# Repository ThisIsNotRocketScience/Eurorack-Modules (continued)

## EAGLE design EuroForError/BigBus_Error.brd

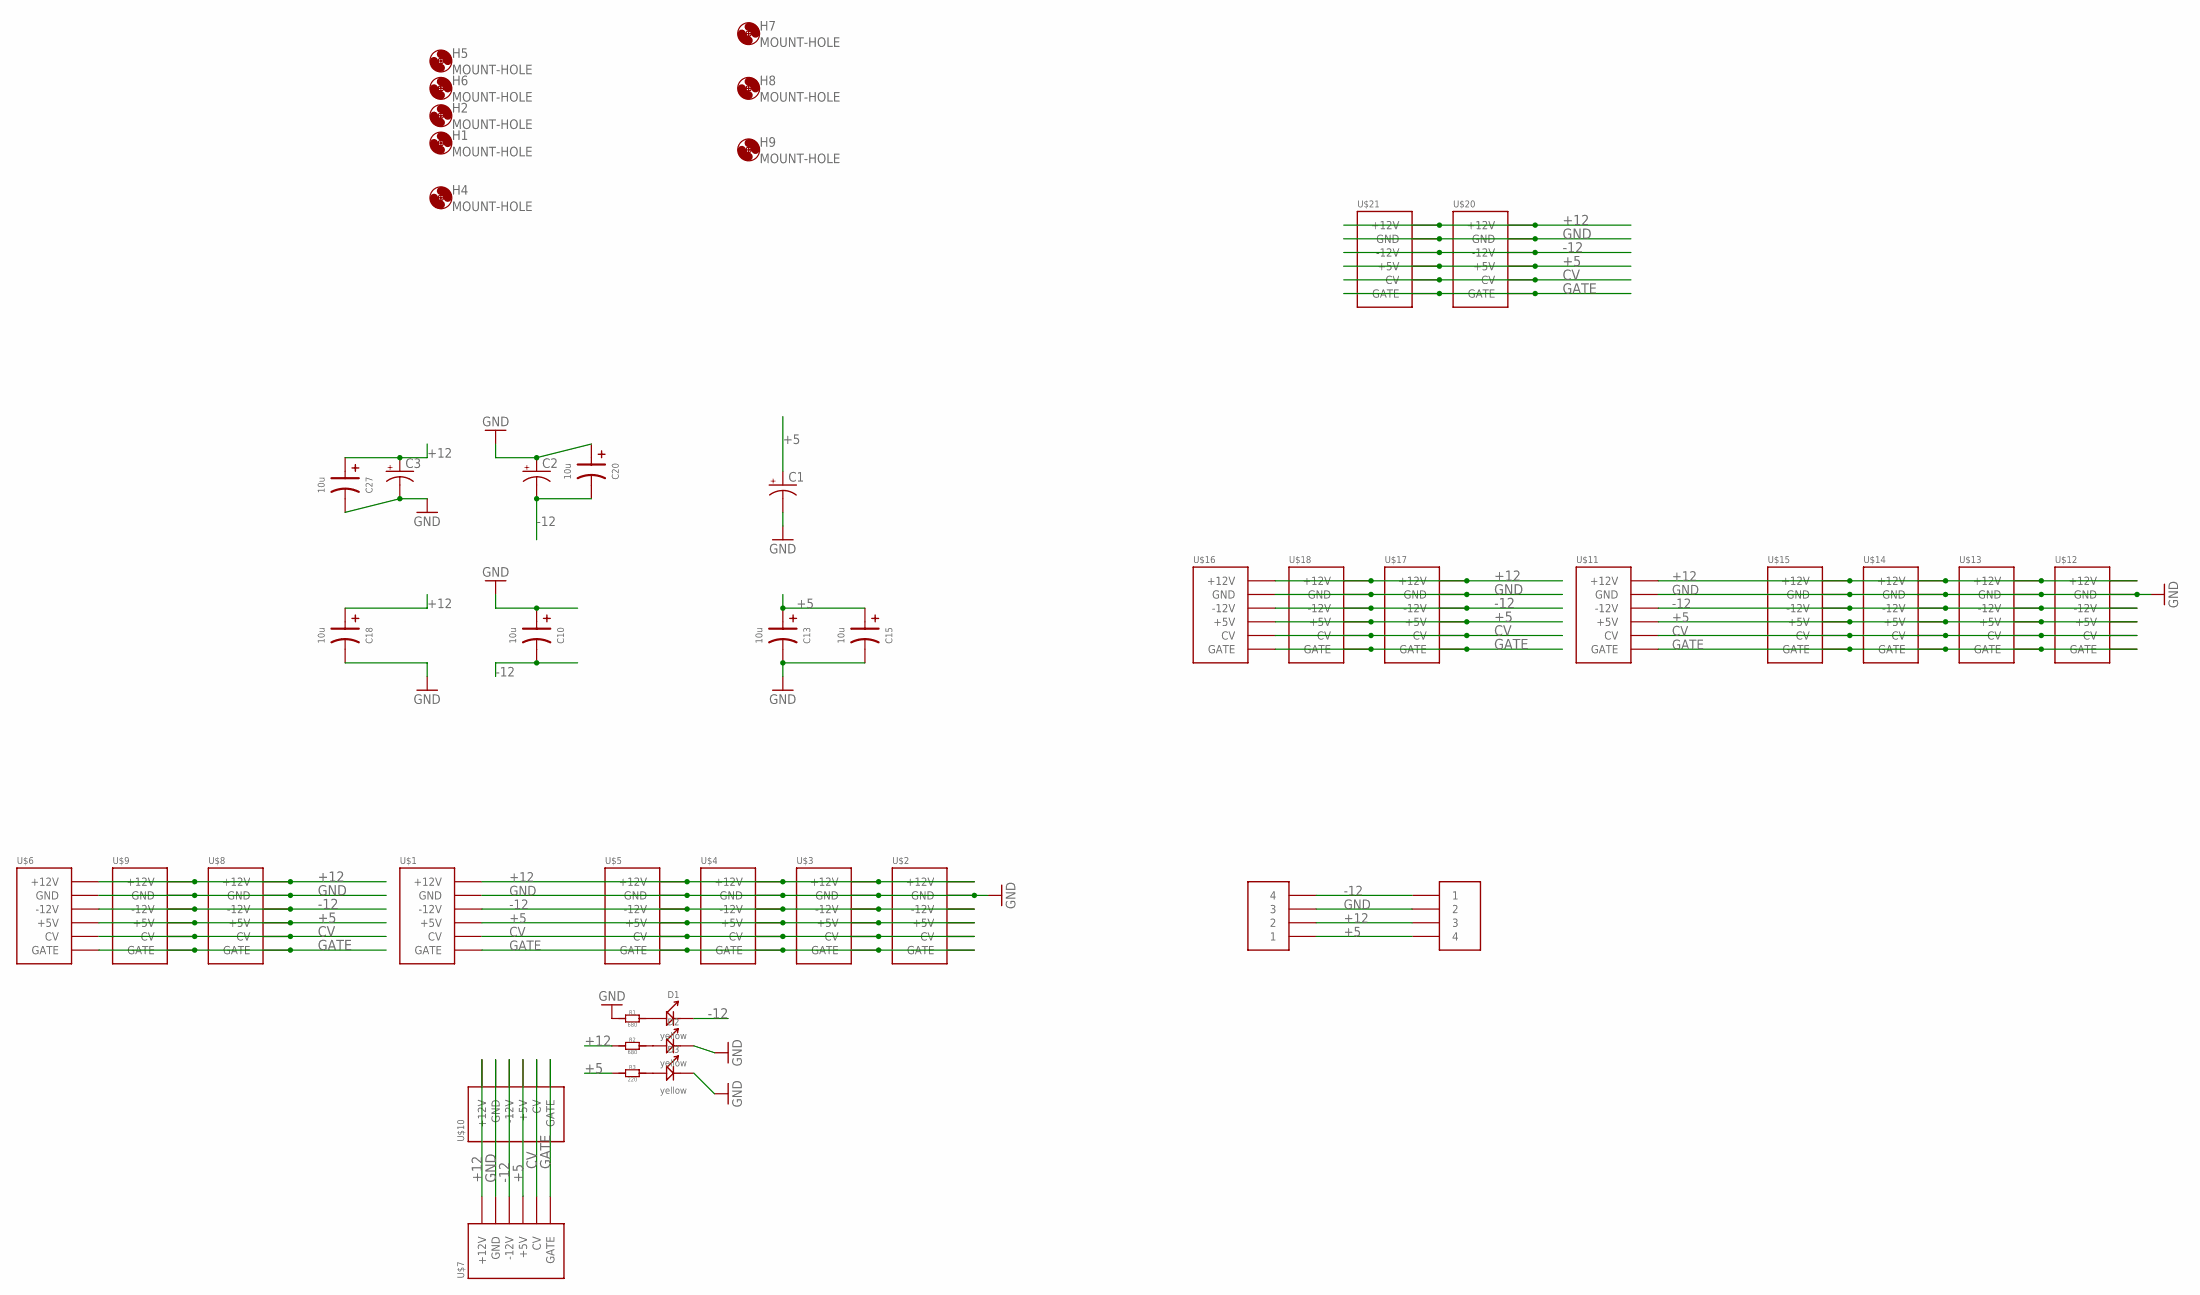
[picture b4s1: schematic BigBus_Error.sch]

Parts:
C1, C2, C3: CAP_POLD; PANASONIC_D
C10, C13, C15, C18, C20, C27: 10u; AVX-A
D1, D2, D3: yellow; LED0603
H1, H2, H4, H5, H6, H7, H8, H9: MOUNT-HOLE; 3.2-NOMARKINGS-SMALLSAFEZONE
R1, R2: 680; R0603
R3: 220; R0603
U$1, U$2, U$3, U$4, U$5, U$6, U$7, U$8, U$9, U$10, U$11, U$12, U$13, U$14, U$15, U$16, U$17, U$18, U$20, U$21: POWER_SHROUDED_NOTEXT; POWER_16_SHROUDED_NOTEXT
U$19, U$22: 4PIN5MM

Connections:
+5: C1.+, C13.+ (1), C15.+ (1), R3.1, U$1.11 (+5V), U$1.12 (+5V), U$2.11 (+5V), U$2.12 (+5V), U$3.11 (+5V), U$3.12 (+5V), U$4.11 (+5V), U$4.12 (+5V), U$5.11 (+5V), U$5.12 (+5V), U$6.11 (+5V), U$6.12 (+5V), U$7.11 (+5V), U$7.12 (+5V), U$8.11 (+5V), U$8.12 (+5V), U$9.11 (+5V), U$9.12 (+5V), U$10.11 (+5V), U$10.12 (+5V), U$11.11 (+5V), U$11.12 (+5V), U$12.11 (+5V), U$12.12 (+5V), U$13.11 (+5V), U$13.12 (+5V), U$14.11 (+5V), U$14.12 (+5V), U$15.11 (+5V), U$15.12 (+5V), U$16.11 (+5V), U$16.12 (+5V), U$17.11 (+5V), U$17.12 (+5V), U$18.11 (+5V), U$18.12 (+5V), U$19.4, U$20.11 (+5V), U$20.12 (+5V), U$21.11 (+5V), U$21.12 (+5V), U$22.1
+12: C3.+, C18.+ (1), C27.+ (1), R2.1, U$1.9 (+12V), U$1.10 (+12V), U$2.9 (+12V), U$2.10 (+12V), U$3.9 (+12V), U$3.10 (+12V), U$4.9 (+12V), U$4.10 (+12V), U$5.9 (+12V), U$5.10 (+12V), U$6.9 (+12V), U$6.10 (+12V), U$7.9 (+12V), U$7.10 (+12V), U$8.9 (+12V), U$8.10 (+12V), U$9.9 (+12V), U$9.10 (+12V), U$10.9 (+12V), U$10.10 (+12V), U$11.9 (+12V), U$11.10 (+12V), U$12.9 (+12V), U$12.10 (+12V), U$13.9 (+12V), U$13.10 (+12V), U$14.9 (+12V), U$14.10 (+12V), U$15.9 (+12V), U$15.10 (+12V), U$16.9 (+12V), U$16.10 (+12V), U$17.9 (+12V), U$17.10 (+12V), U$18.9 (+12V), U$18.10 (+12V), U$19.3, U$20.9 (+12V), U$20.10 (+12V), U$21.9 (+12V), U$21.10 (+12V), U$22.2
-12: C2.-, C10.- (2), C20.- (2), D1.-, U$1.1 (-12V), U$1.2 (-12V), U$2.1 (-12V), U$2.2 (-12V), U$3.1 (-12V), U$3.2 (-12V), U$4.1 (-12V), U$4.2 (-12V), U$5.1 (-12V), U$5.2 (-12V), U$6.1 (-12V), U$6.2 (-12V), U$7.1 (-12V), U$7.2 (-12V), U$8.1 (-12V), U$8.2 (-12V), U$9.1 (-12V), U$9.2 (-12V), U$10.1 (-12V), U$10.2 (-12V), U$11.1 (-12V), U$11.2 (-12V), U$12.1 (-12V), U$12.2 (-12V), U$13.1 (-12V), U$13.2 (-12V), U$14.1 (-12V), U$14.2 (-12V), U$15.1 (-12V), U$15.2 (-12V), U$16.1 (-12V), U$16.2 (-12V), U$17.1 (-12V), U$17.2 (-12V), U$18.1 (-12V), U$18.2 (-12V), U$19.1, U$20.1 (-12V), U$20.2 (-12V), U$21.1 (-12V), U$21.2 (-12V), U$22.4
CV: U$1.13 (CV), U$1.14 (CV), U$2.13 (CV), U$2.14 (CV), U$3.13 (CV), U$3.14 (CV), U$4.13 (CV), U$4.14 (CV), U$5.13 (CV), U$5.14 (CV), U$6.13 (CV), U$6.14 (CV), U$7.13 (CV), U$7.14 (CV), U$8.13 (CV), U$8.14 (CV), U$9.13 (CV), U$9.14 (CV), U$10.13 (CV), U$10.14 (CV), U$11.13 (CV), U$11.14 (CV), U$12.13 (CV), U$12.14 (CV), U$13.13 (CV), U$13.14 (CV), U$14.13 (CV), U$14.14 (CV), U$15.13 (CV), U$15.14 (CV), U$16.13 (CV), U$16.14 (CV), U$17.13 (CV), U$17.14 (CV), U$18.13 (CV), U$18.14 (CV), U$20.13 (CV), U$20.14 (CV), U$21.13 (CV), U$21.14 (CV)
GATE: U$1.15 (GATE), U$1.16 (GATE), U$2.15 (GATE), U$2.16 (GATE), U$3.15 (GATE), U$3.16 (GATE), U$4.15 (GATE), U$4.16 (GATE), U$5.15 (GATE), U$5.16 (GATE), U$6.15 (GATE), U$6.16 (GATE), U$7.15 (GATE), U$7.16 (GATE), U$8.15 (GATE), U$8.16 (GATE), U$9.15 (GATE), U$9.16 (GATE), U$10.15 (GATE), U$10.16 (GATE), U$11.15 (GATE), U$11.16 (GATE), U$12.15 (GATE), U$12.16 (GATE), U$13.15 (GATE), U$13.16 (GATE), U$14.15 (GATE), U$14.16 (GATE), U$15.15 (GATE), U$15.16 (GATE), U$16.15 (GATE), U$16.16 (GATE), U$17.15 (GATE), U$17.16 (GATE), U$18.15 (GATE), U$18.16 (GATE), U$20.15 (GATE), U$20.16 (GATE), U$21.15 (GATE), U$21.16 (GATE)
GND: C1.-, C2.+, C3.-, C10.+ (1), C13.- (2), C15.- (2), C18.- (2), C20.+ (1), C27.- (2), D2.-, D3.-, R1.1, U$1.3 (GND), U$1.4 (GND), U$1.5 (GND), U$1.6 (GND), U$1.7 (GND), U$1.8 (GND), U$2.3 (GND), U$2.4 (GND), U$2.5 (GND), U$2.6 (GND), U$2.7 (GND), U$2.8 (GND), U$3.3 (GND), U$3.4 (GND), U$3.5 (GND), U$3.6 (GND), U$3.7 (GND), U$3.8 (GND), U$4.3 (GND), U$4.4 (GND), U$4.5 (GND), U$4.6 (GND), U$4.7 (GND), U$4.8 (GND), U$5.3 (GND), U$5.4 (GND), U$5.5 (GND), U$5.6 (GND), U$5.7 (GND), U$5.8 (GND), U$6.3 (GND), U$6.4 (GND), U$6.5 (GND), U$6.6 (GND), U$6.7 (GND), U$6.8 (GND), U$7.3 (GND), U$7.4 (GND), U$7.5 (GND), U$7.6 (GND), U$7.7 (GND), U$7.8 (GND), U$8.3 (GND), U$8.4 (GND), U$8.5 (GND), U$8.6 (GND), U$8.7 (GND), U$8.8 (GND), U$9.3 (GND), U$9.4 (GND), U$9.5 (GND), U$9.6 (GND), U$9.7 (GND), U$9.8 (GND), U$10.3 (GND), U$10.4 (GND), U$10.5 (GND), U$10.6 (GND), U$10.7 (GND), U$10.8 (GND), U$11.3 (GND), U$11.4 (GND), U$11.5 (GND), U$11.6 (GND), U$11.7 (GND), U$11.8 (GND), U$12.3 (GND), U$12.4 (GND), U$12.5 (GND), U$12.6 (GND), U$12.7 (GND), U$12.8 (GND), U$13.3 (GND), U$13.4 (GND), U$13.5 (GND), U$13.6 (GND), U$13.7 (GND), U$13.8 (GND), U$14.3 (GND), U$14.4 (GND), U$14.5 (GND), U$14.6 (GND), U$14.7 (GND), U$14.8 (GND), U$15.3 (GND), U$15.4 (GND), U$15.5 (GND), U$15.6 (GND), U$15.7 (GND), U$15.8 (GND), U$16.3 (GND), U$16.4 (GND), U$16.5 (GND), U$16.6 (GND), U$16.7 (GND), U$16.8 (GND), U$17.3 (GND), U$17.4 (GND), U$17.5 (GND), U$17.6 (GND), U$17.7 (GND), U$17.8 (GND), U$18.3 (GND), U$18.4 (GND), U$18.5 (GND), U$18.6 (GND), U$18.7 (GND), U$18.8 (GND), U$19.2, U$20.3 (GND), U$20.4 (GND), U$20.5 (GND), U$20.6 (GND), U$20.7 (GND), U$20.8 (GND), U$21.3 (GND), U$21.4 (GND), U$21.5 (GND), U$21.6 (GND), U$21.7 (GND), U$21.8 (GND), U$22.3
unnamed: D1.+, R1.2
unnamed: D2.+, R2.2
unnamed: D3.+, R3.2

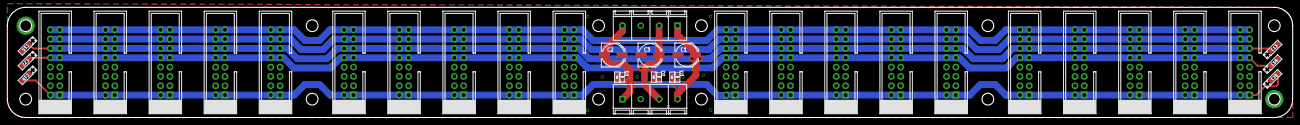
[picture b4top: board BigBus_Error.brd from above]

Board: 2 copper layers, 350.0 x 30.0 mm, 47 parts (0 on the bottom side), 9 nets.

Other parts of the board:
H11, H12: MOUNT-HOLE; 3.2-NOMARKINGS-SMALLSAFEZONE

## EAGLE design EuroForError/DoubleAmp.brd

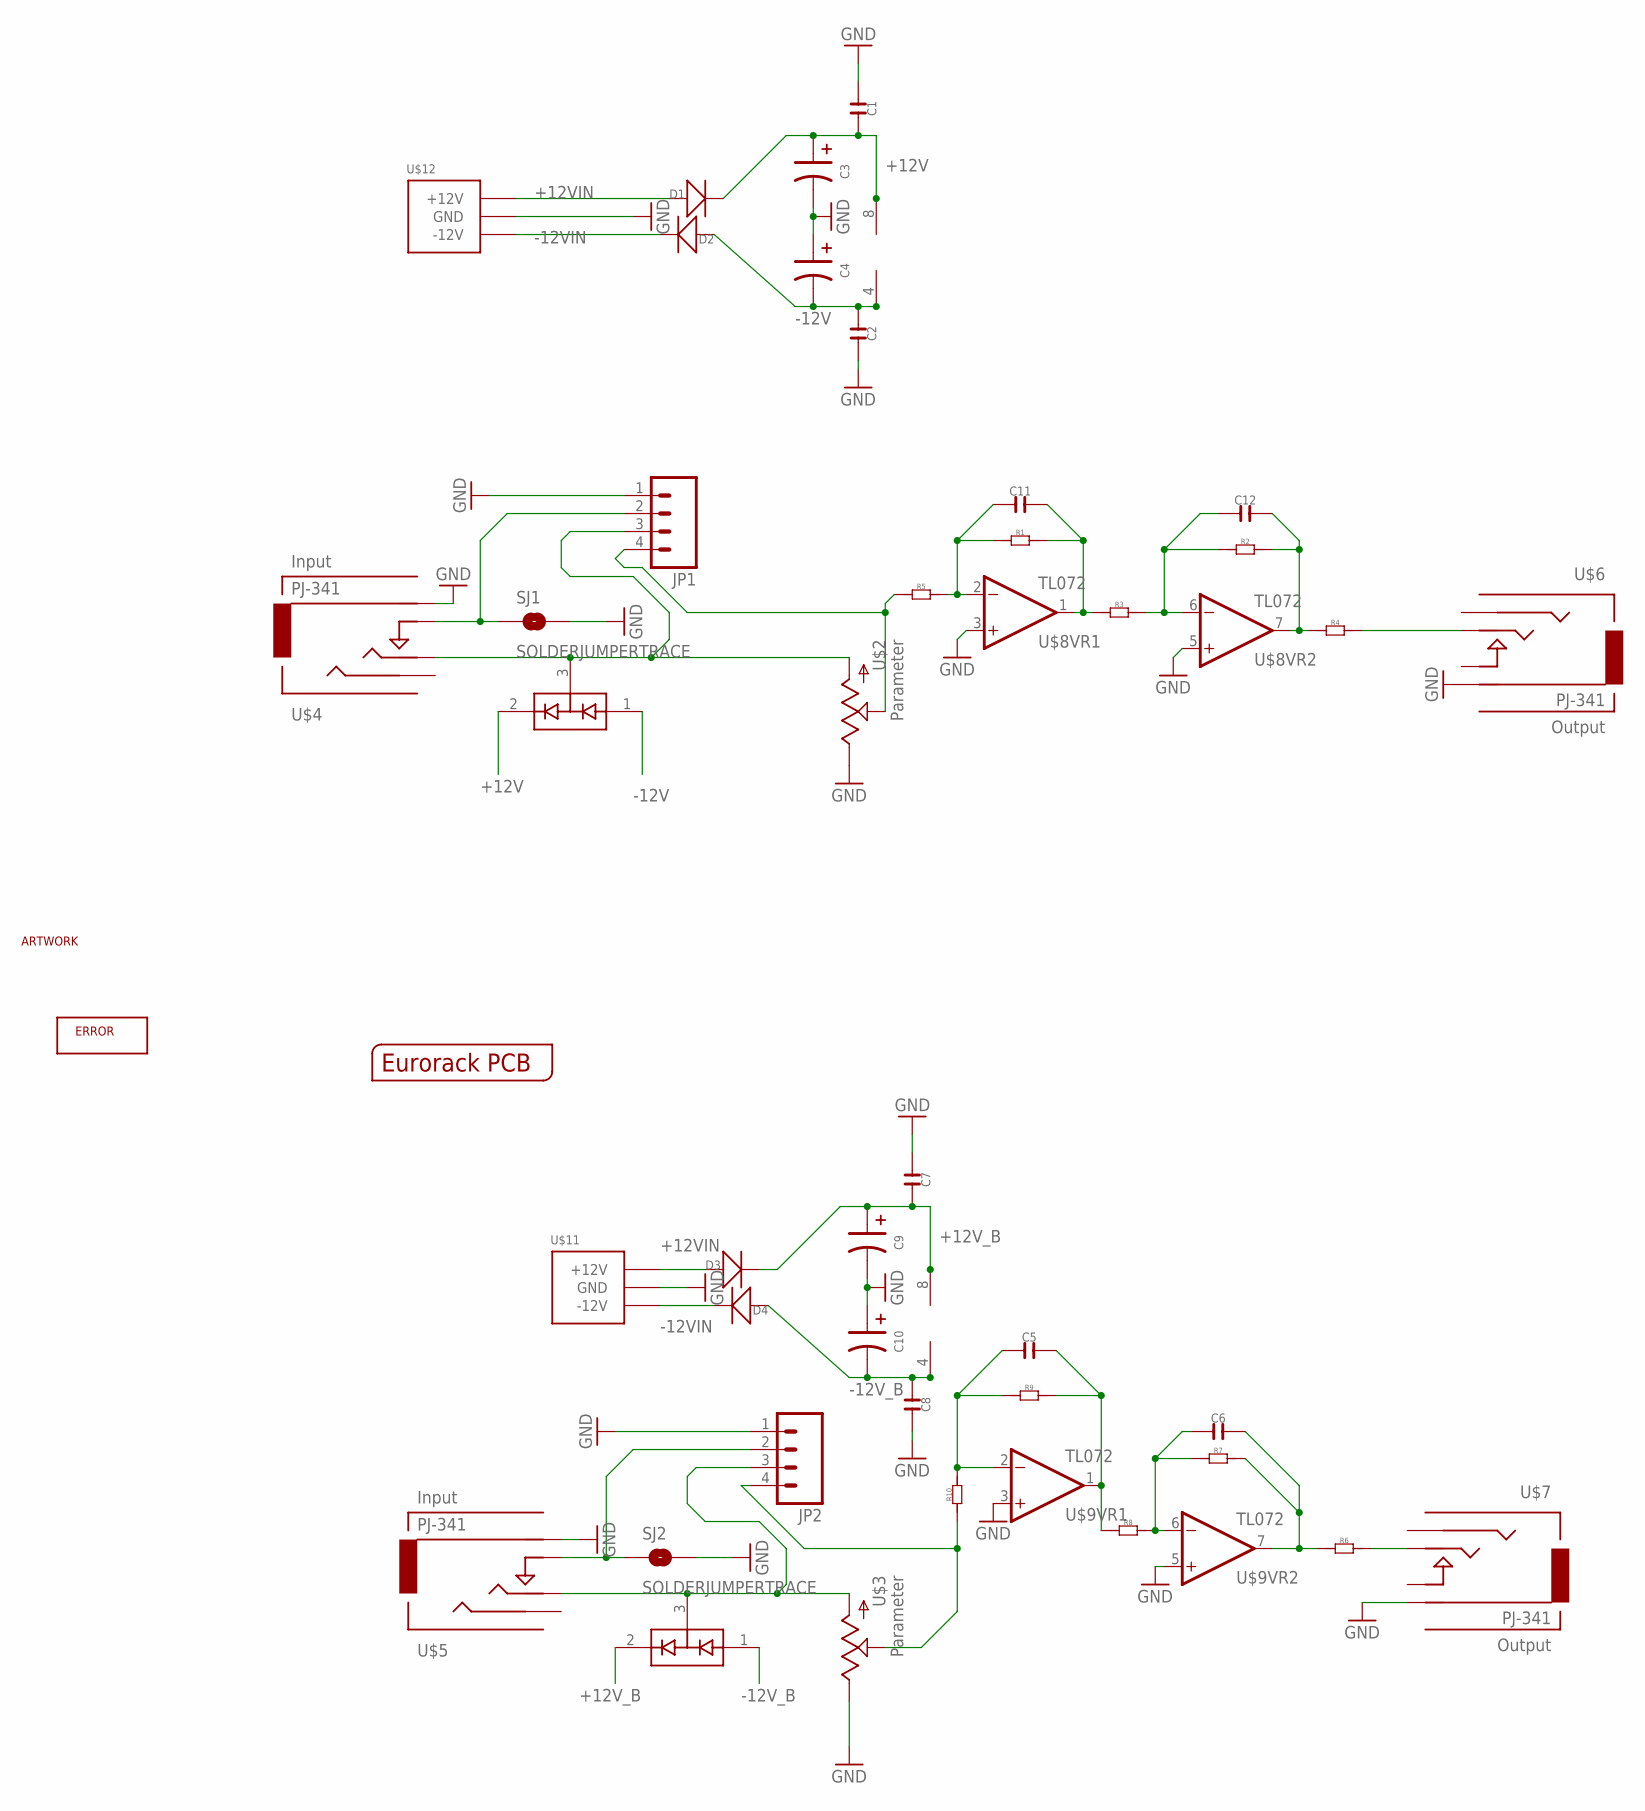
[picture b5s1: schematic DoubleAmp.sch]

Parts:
C1, C2, C5, C6, C7, C8, C11, C12: C-0603; C0603
C3, C4, C9, C10: C-POLAR-A; AVX-A
D1, D2, D3, D4: D-SMA; DO-214AC
D5, D6: BAV99; SOT23
JP1, JP2: M04PTH; 1X04
R1, R2, R3, R4, R5, R6, R7, R8, R9, R10: R-0603; R0603
SJ1, SJ2: SOLDERJUMPERTRACE; SJ_2S-TRACE
U$1: EURORACK_PCB4HP; EURORACK4HPPCB
U$2, U$3: POTZEPHPOT; OG-POTS_ALPS_POT_VERTICAL
U$4, U$5: PJ-341; 3.5MM-JACK-SWITCH-13MM-INPUT
U$6, U$7: PJ-341; 3.5MM-JACK-SWITCH-13MM-OUTPUT
U$8, U$9: TL072; SO08
U$10: ERRORLOGO
U$11, U$12: POWER_SIMPLE; 2X05_SMT_HEADER
U$13: TINRS_ARTWORKROCKET; TINRS_ROCKET

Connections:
+12V: C1.2, C3.+ (1), D1.2 (-), D6.2 (C2), U$8.8 (V+)
+12VIN: D1.1 (+), D3.1 (+), U$11.9 (+12V), U$11.10 (+12V), U$12.9 (+12V), U$12.10 (+12V)
+12V_B: C7.2, C9.+ (1), D3.2 (-), D5.2 (C2), U$9.8 (V+)
-12V: C2.1, C4.- (2), D2.1 (+), D6.1 (A1), U$8.4 (V-)
-12VIN: D2.2 (-), D4.2 (-), U$11.1 (-12V), U$11.2 (-12V), U$12.1 (-12V), U$12.2 (-12V)
-12V_B: C8.1, C10.- (2), D4.1 (+), D5.1 (A1), U$9.4 (V-)
GND: C1.1, C2.2, C3.- (2), C4.+ (1), C7.1, C8.2, C9.- (2), C10.+ (1), JP1.1, JP2.1, SJ1.2, SJ2.2, U$2.P$1 (E), U$3.P$1 (E), U$4.RING@3 (RING), U$5.RING@3 (RING), U$6.RING@3 (RING), U$7.RING@3 (RING), U$8.3 (+IN), U$8.5 (+IN), U$9.3 (+IN), U$9.5 (+IN), U$11.3 (GND), U$11.4 (GND), U$11.5 (GND), U$11.6 (GND), U$11.7 (GND), U$11.8 (GND), U$12.3 (GND), U$12.4 (GND), U$12.5 (GND), U$12.6 (GND), U$12.7 (GND), U$12.8 (GND)
unnamed: D6.3 (COM), JP1.3, U$2.P$3 (A), U$4.TIP@3 (TIP)
unnamed: R4.2, U$6.TIP@3 (TIP)
unnamed: R6.2, U$7.TIP@3 (TIP)
unnamed: D5.3 (COM), JP2.3, U$3.P$3 (A), U$5.TIP@3 (TIP)
unnamed: JP2.4, R10.1, U$3.P$2 (S)
unnamed: C11.2, R1.2, R3.1, U$8.1 (OUT)
unnamed: C6.2, R6.1, R7.2, U$9.7 (OUT)
unnamed: C6.1, R7.1, R8.2, U$9.6 (-IN)
unnamed: C5.1, R9.1, R10.2, U$9.2 (-IN)
unnamed: C12.1, R2.1, R3.2, U$8.6 (-IN)
unnamed: C12.2, R2.2, R4.1, U$8.7 (OUT)
unnamed: C11.1, R1.1, R5.2, U$8.2 (-IN)
unnamed: JP1.2, SJ1.1, U$4.SWITCH@3 (SWITCH)
unnamed: JP1.4, R5.1, U$2.P$2 (S)
unnamed: C5.2, R8.1, R9.2, U$9.1 (OUT)
unnamed: JP2.2, SJ2.1, U$5.SWITCH@3 (SWITCH)

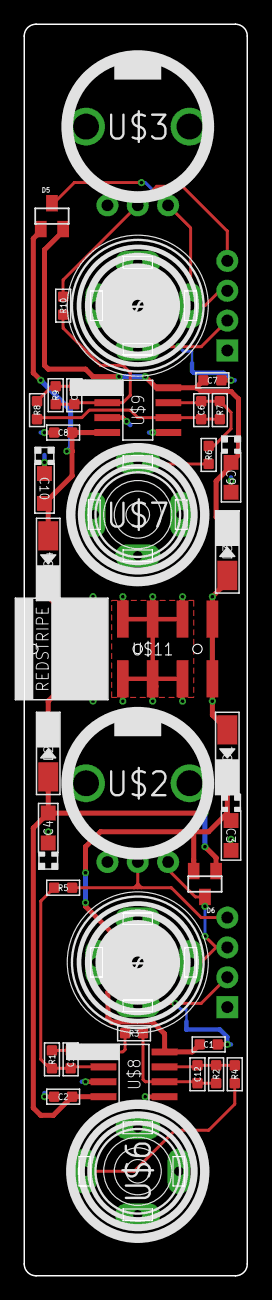
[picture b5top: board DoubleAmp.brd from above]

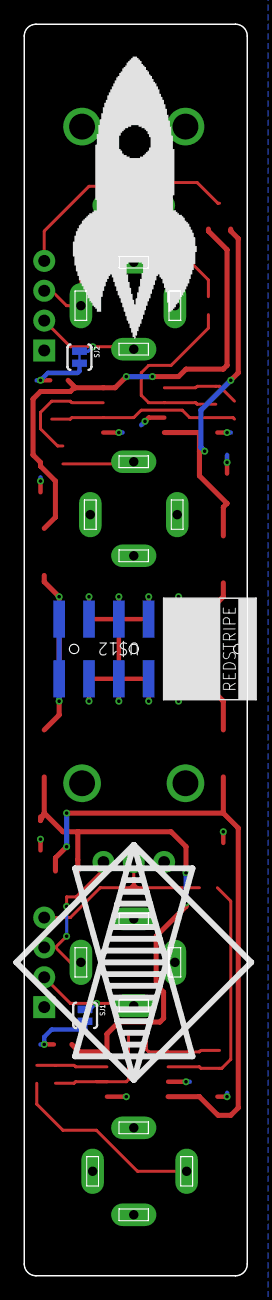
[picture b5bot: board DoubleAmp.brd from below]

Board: 2 copper layers, 19.0 x 106.5 mm, 45 parts (5 on the bottom side), 23 nets.

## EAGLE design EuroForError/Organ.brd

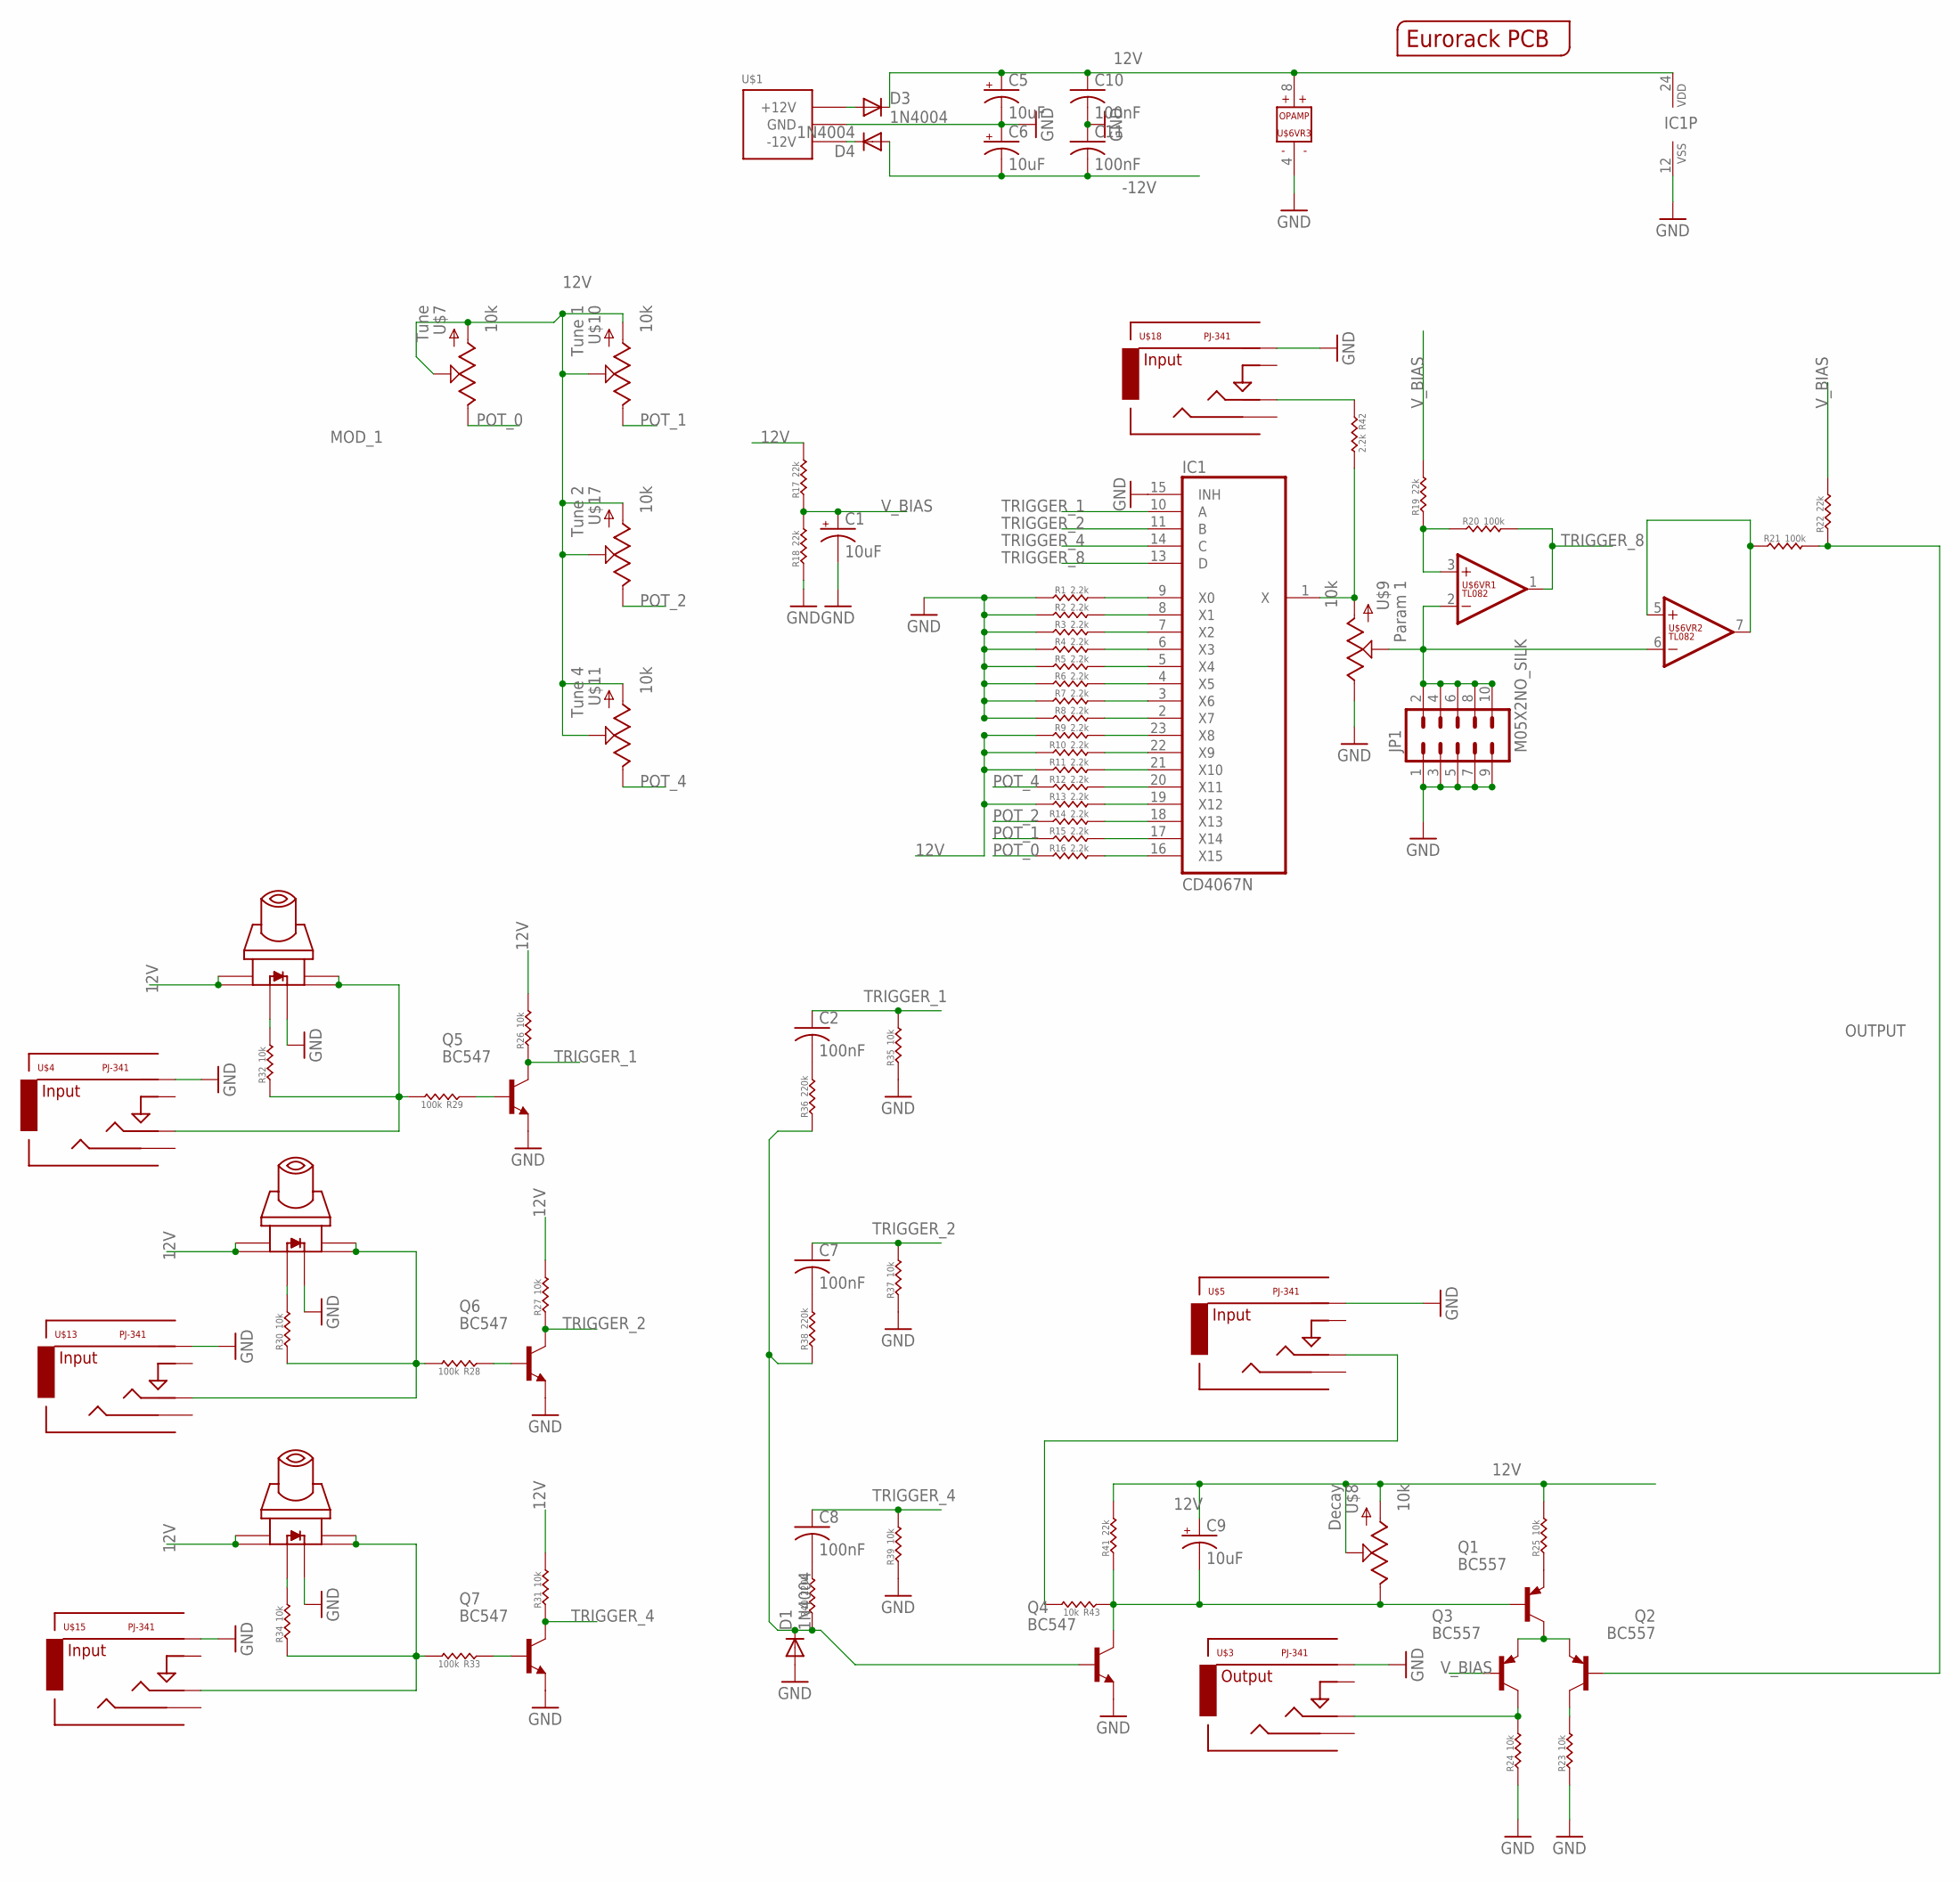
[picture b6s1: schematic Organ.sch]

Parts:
C1, C5, C6, C9: 10uF; E5-6
C2, C7, C8, C10, C11: 100nF; C050-025X075
D1, D3, D4: 1N4004; DO41-10
IC1: CD4067N; DIL24-6
JP1: M05X2NO_SILK; 2X5_NOSILK
Q1, Q2, Q3: BC557; TO92
Q4, Q5, Q6, Q7: BC547; TO92
R1, R2, R3, R4, R5, R6, R7, R8, R9, R10, R11, R12, R13, R14, R15, R16, R42: 2.2k; 0204/5
R17, R18, R19, R22, R41: 22k; 0204/5
R20, R21, R28, R29, R33: 100k; 0204/5
R23, R24, R25, R26, R27, R30, R31, R32, R34, R35, R37, R39, R43: 10k; 0204/5
R36, R38, R40: 220k; 0204/5
U$1: POWER_SIMPLE10; POWER_10
U$2: EURORACK_PCB12HP; EURORACK12HPPCB
U$3: PJ-341; 3.5MM-JACK-SWITCH-13MM-OUTPUT
U$4, U$5, U$13, U$15, U$18: PJ-341; 3.5MM-JACK-SWITCH-13MM-INPUT
U$6: TL082; DIL08
U$7, U$8, U$9, U$10, U$11, U$17: 10k; OG-POTS_ALPS_POT_VERTICAL
U$12, U$14, U$16: SWITCH_W_LED_PB6149L-X-102YELLOW; PB6149L

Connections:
12V: C5.+, C9.+, C10.1, D3.C, IC1.24 (VDD), R9.1, R10.1, R11.1, R13.1, R17.2, R25.2, R26.2, R27.2, R31.2, R41.2, U$6.8 (V+), U$7.P$2 (S), U$7.P$3 (A), U$8.P$2 (S), U$8.P$3 (A), U$10.P$2 (S), U$10.P$3 (A), U$11.P$2 (S), U$11.P$3 (A), U$12.1, U$12.2, U$14.1, U$14.2, U$16.1, U$16.2, U$17.P$2 (S), U$17.P$3 (A)
-12V: C6.-, C11.2, D4.A
GND: C1.-, C5.-, C6.+, C10.2, C11.1, D1.A, IC1.12 (VSS), IC1.15 (INH), JP1.1, JP1.3, JP1.5, JP1.7, JP1.9, Q4.1 (E), Q5.1 (E), Q6.1 (E), Q7.1 (E), R1.1, R2.1, R3.1, R4.1, R5.1, R6.1, R7.1, R8.1, R18.1, R23.1, R24.1, R35.1, R37.1, R39.1, U$1.3 (GND), U$1.4 (GND), U$1.5 (GND), U$1.6 (GND), U$1.7 (GND), U$1.8 (GND), U$3.RING@3 (RING), U$4.RING@3 (RING), U$5.RING@3 (RING), U$6.4 (V-), U$9.P$1 (E), U$12.LEDNEG (NEG), U$13.RING@3 (RING), U$14.LEDNEG (NEG), U$15.RING@3 (RING), U$16.LEDNEG (NEG), U$18.RING@3 (RING)
MOD_1: IC1.1 (X), R42.2, U$9.P$3 (A)
unnamed: IC1.9 (X0), R1.2
unnamed: IC1.8 (X1), R2.2
unnamed: IC1.7 (X2), R3.2
unnamed: IC1.6 (X3), R4.2
unnamed: IC1.5 (X4), R5.2
unnamed: IC1.4 (X5), R6.2
unnamed: IC1.3 (X6), R7.2
unnamed: IC1.2 (X7), R8.2
unnamed: IC1.23 (X8), R9.2
unnamed: IC1.22 (X9), R10.2
unnamed: IC1.21 (X10), R11.2
unnamed: IC1.20 (X11), R12.2
unnamed: IC1.19 (X12), R13.2
unnamed: IC1.18 (X13), R14.2
unnamed: IC1.17 (X14), R15.2
unnamed: IC1.16 (X15), R16.2
unnamed: D3.A, U$1.9 (+12V), U$1.10 (+12V)
unnamed: D4.C, U$1.1 (-12V), U$1.2 (-12V)
unnamed: R21.1, U$6.5 (+IN), U$6.7 (OUT)
unnamed: JP1.2, JP1.4, JP1.6, JP1.8, JP1.10, U$6.2 (-IN), U$6.6 (-IN), U$9.P$2 (S)
unnamed: Q1.3 (C), Q2.1 (E), Q3.1 (E)
unnamed: R19.1, R20.1, U$6.3 (+IN)
unnamed: R42.1, U$18.TIP@3 (TIP)
unnamed: Q2.3 (C), R23.2
unnamed: Q3.3 (C), R24.2, U$3.TIP@3 (TIP)
unnamed: R43.2, U$5.TIP@3 (TIP)
unnamed: Q1.1 (E), R25.1
unnamed: C2.2, R36.2
unnamed: C9.-, Q1.2 (B), Q4.3 (C), R41.1, R43.1, U$8.P$1 (E)
unnamed: Q6.2 (B), R28.1
unnamed: Q5.2 (B), R29.1
unnamed: R28.2, R30.1, U$13.TIP@3 (TIP), U$14.3, U$14.4
unnamed: R30.2, U$14.LEDPOS (POS)
unnamed: R29.2, R32.1, U$4.TIP@3 (TIP), U$12.3, U$12.4
unnamed: R32.2, U$12.LEDPOS (POS)
unnamed: D1.C, Q4.2 (B), R36.1, R38.1, R40.1
unnamed: Q7.2 (B), R33.1
unnamed: R33.2, R34.1, U$15.TIP@3 (TIP), U$16.3, U$16.4
unnamed: R34.2, U$16.LEDPOS (POS)
unnamed: C7.2, R38.2
unnamed: C8.2, R40.2
OUTPUT: Q2.2 (B), R21.2, R22.1
POT_0: R16.1, U$7.P$1 (E)
POT_1: R15.1, U$10.P$1 (E)
POT_2: R14.1, U$17.P$1 (E)
POT_4: R12.1, U$11.P$1 (E)
TRIGGER_1: C2.1, IC1.10 (A), Q5.3 (C), R26.1, R35.2
TRIGGER_2: C7.1, IC1.11 (B), Q6.3 (C), R27.1, R37.2
TRIGGER_4: C8.1, IC1.14 (C), Q7.3 (C), R31.1, R39.2
TRIGGER_8: IC1.13 (D), R20.2, U$6.1 (OUT)
V_BIAS: C1.+, Q3.2 (B), R17.1, R18.2, R19.2, R22.2

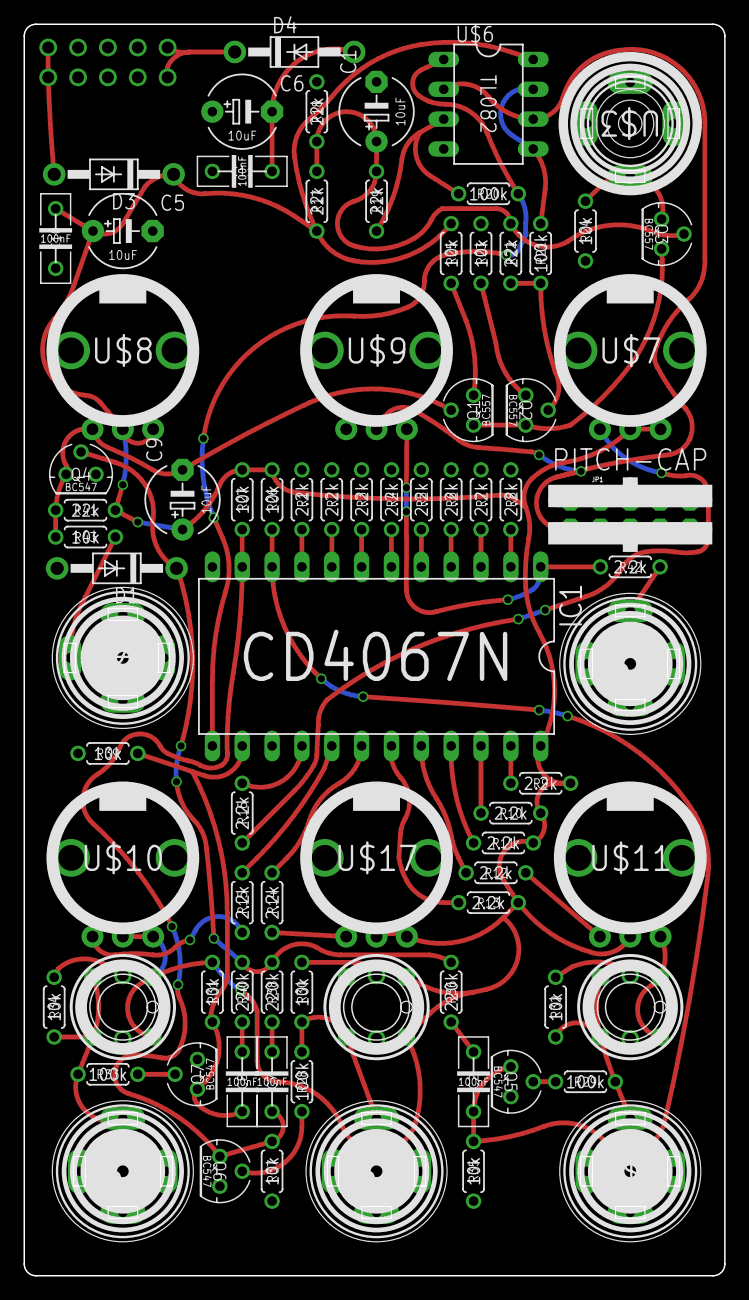
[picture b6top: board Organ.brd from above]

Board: 2 copper layers, 59.6 x 106.5 mm, 82 parts (1 on the bottom side), 55 nets.

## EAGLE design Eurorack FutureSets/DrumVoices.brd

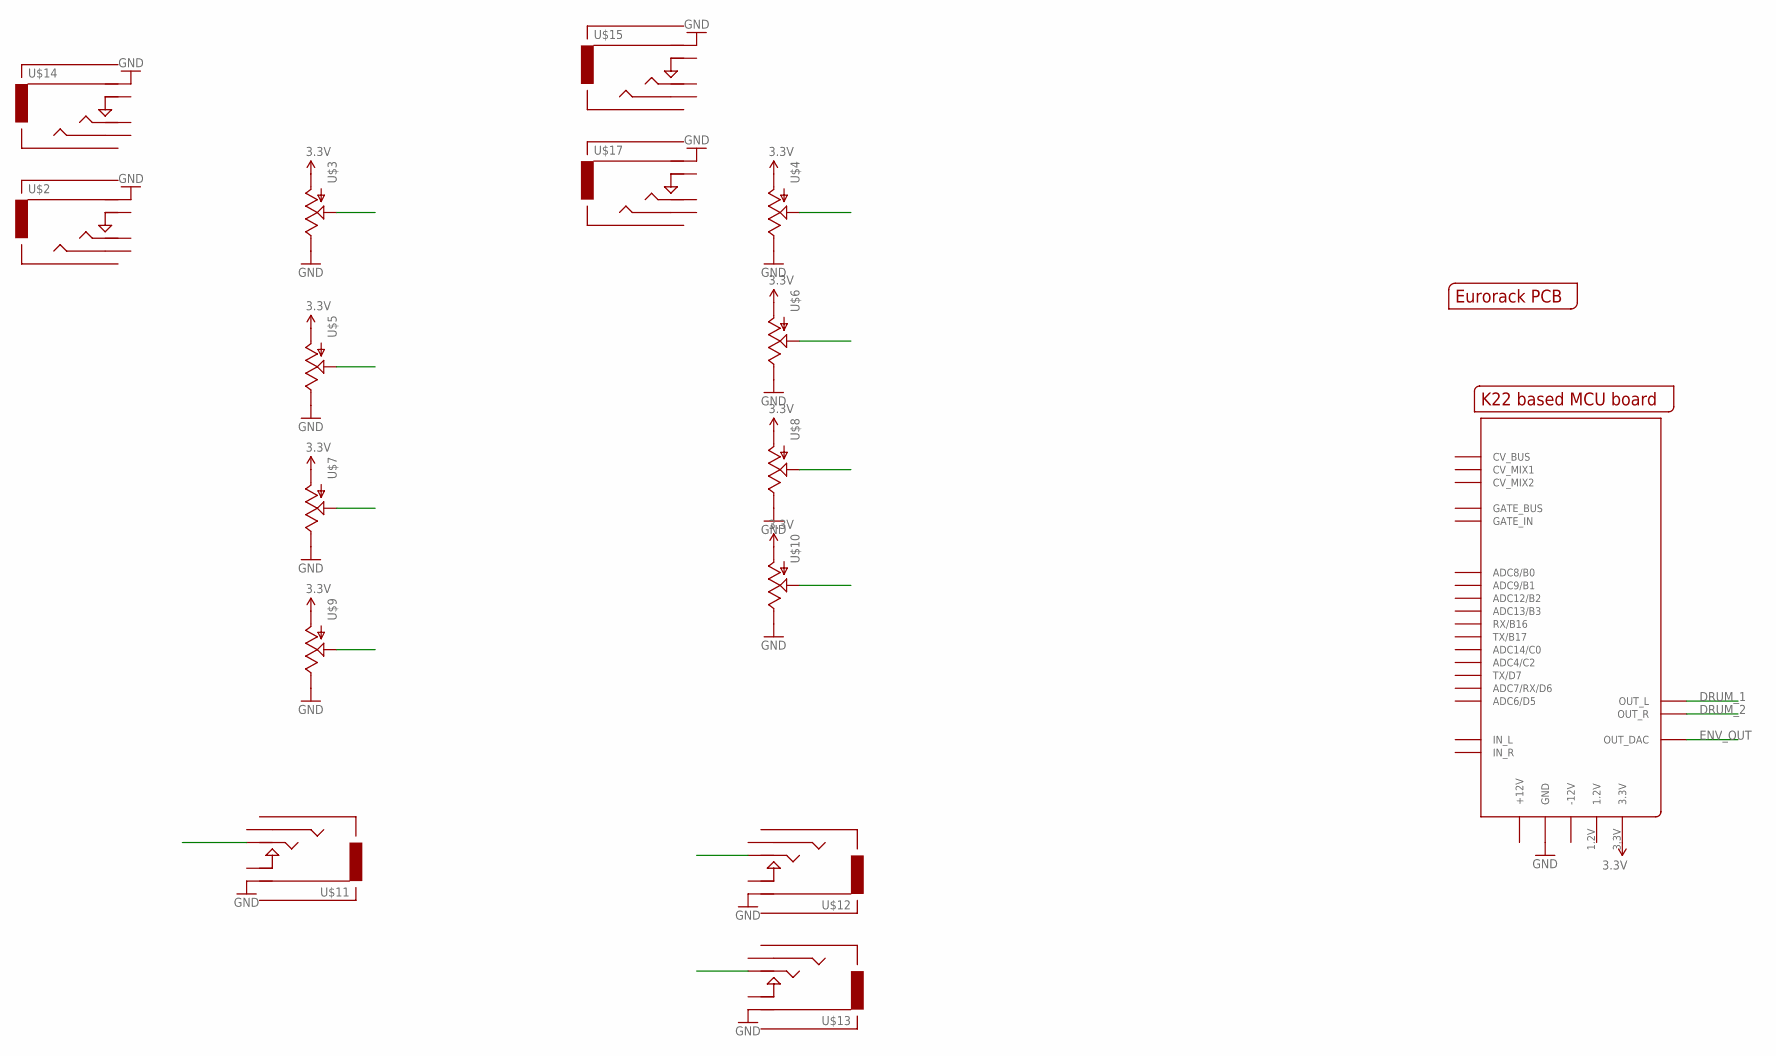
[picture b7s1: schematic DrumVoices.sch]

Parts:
U$1: EURORACK_PCB12HP; EURORACK12HPPCB
U$2, U$14, U$15, U$17: AUDIO-JACKINPUT; 3.5MM-JACK-SWITCH-13MM-INPUT
U$3, U$4, U$5, U$6, U$7, U$8, U$9, U$10: POTZEPHPOT; OG-POTS_ALPS_POT_VERTICAL
U$11, U$12, U$13: AUDIO-JACKOUTPUT; 3.5MM-JACK-SWITCH-13MM-OUTPUT
U$16: MCUBOARD; MCUBASEBOARD

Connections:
3.3V: U$3.P$3 (A), U$4.P$3 (A), U$5.P$3 (A), U$6.P$3 (A), U$7.P$3 (A), U$8.P$3 (A), U$9.P$3 (A), U$10.P$3 (A), U$16.3.3V
DRUM_1: U$11.TIP@1 (TIP), U$11.TIP@2 (TIP), U$16.OUT_L
DRUM_2: U$12.TIP@1 (TIP), U$12.TIP@2 (TIP), U$16.OUT_R
ENV_OUT: U$13.TIP@1 (TIP), U$13.TIP@2 (TIP), U$16.OUT_DAC
GND: U$2.RING@1 (RING), U$2.RING@2 (RING), U$3.P$1 (E), U$4.P$1 (E), U$5.P$1 (E), U$6.P$1 (E), U$7.P$1 (E), U$8.P$1 (E), U$9.P$1 (E), U$10.P$1 (E), U$11.RING@1 (RING), U$11.RING@2 (RING), U$12.RING@1 (RING), U$12.RING@2 (RING), U$13.RING@1 (RING), U$13.RING@2 (RING), U$14.RING@1 (RING), U$14.RING@2 (RING), U$15.RING@1 (RING), U$15.RING@2 (RING), U$16.GND@1 (GND), U$16.GND@2 (GND), U$16.GND@4 (GND), U$16.GND@5 (GND), U$16.GND@6 (GND), U$16.GND@7 (GND), U$16.GND@8 (GND), U$16.GND@9 (GND), U$16.GND_BUS (GND), U$17.RING@1 (RING), U$17.RING@2 (RING)

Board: 2 copper layers, 17 parts (0 on the bottom side), 5 nets, no tracks yet.
